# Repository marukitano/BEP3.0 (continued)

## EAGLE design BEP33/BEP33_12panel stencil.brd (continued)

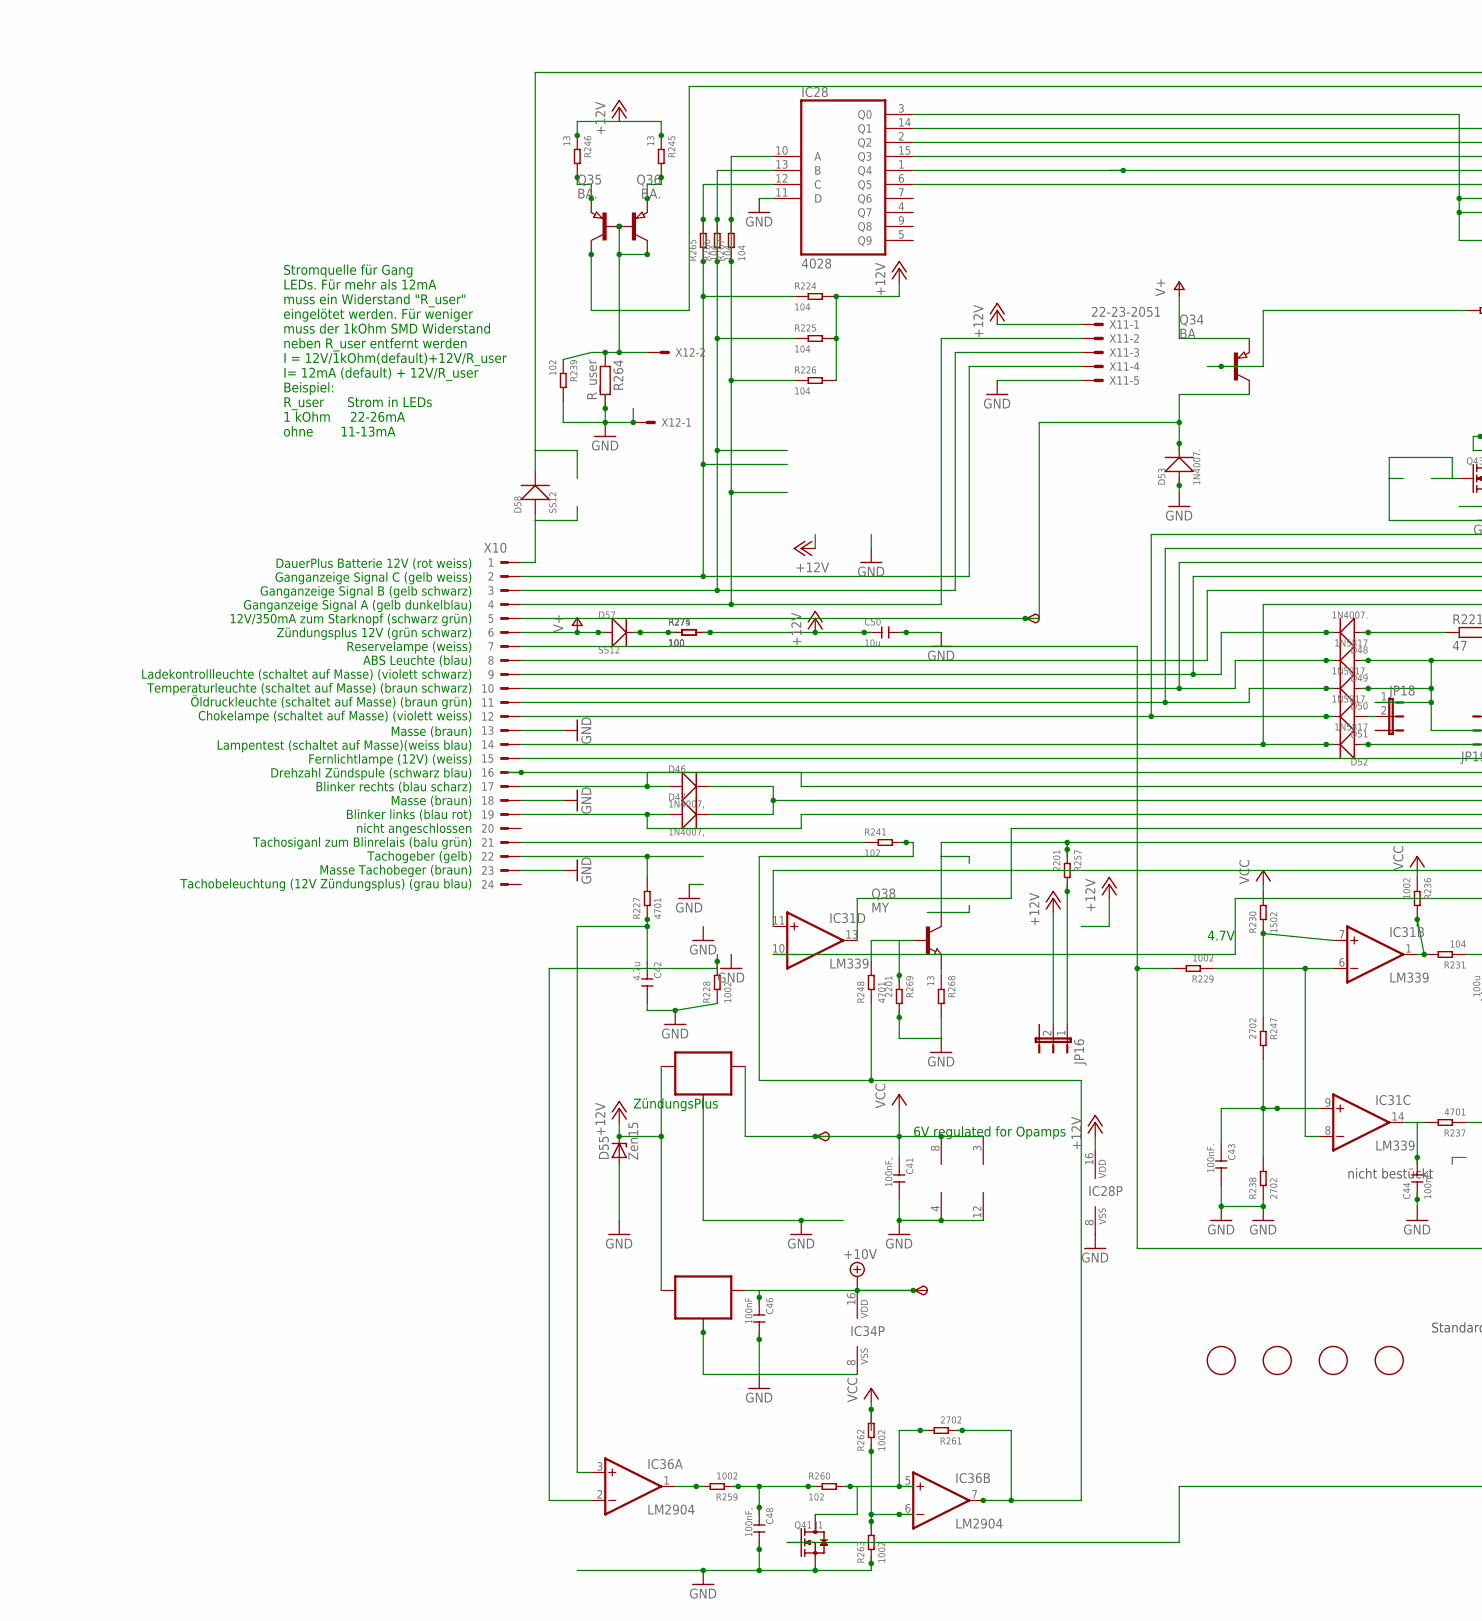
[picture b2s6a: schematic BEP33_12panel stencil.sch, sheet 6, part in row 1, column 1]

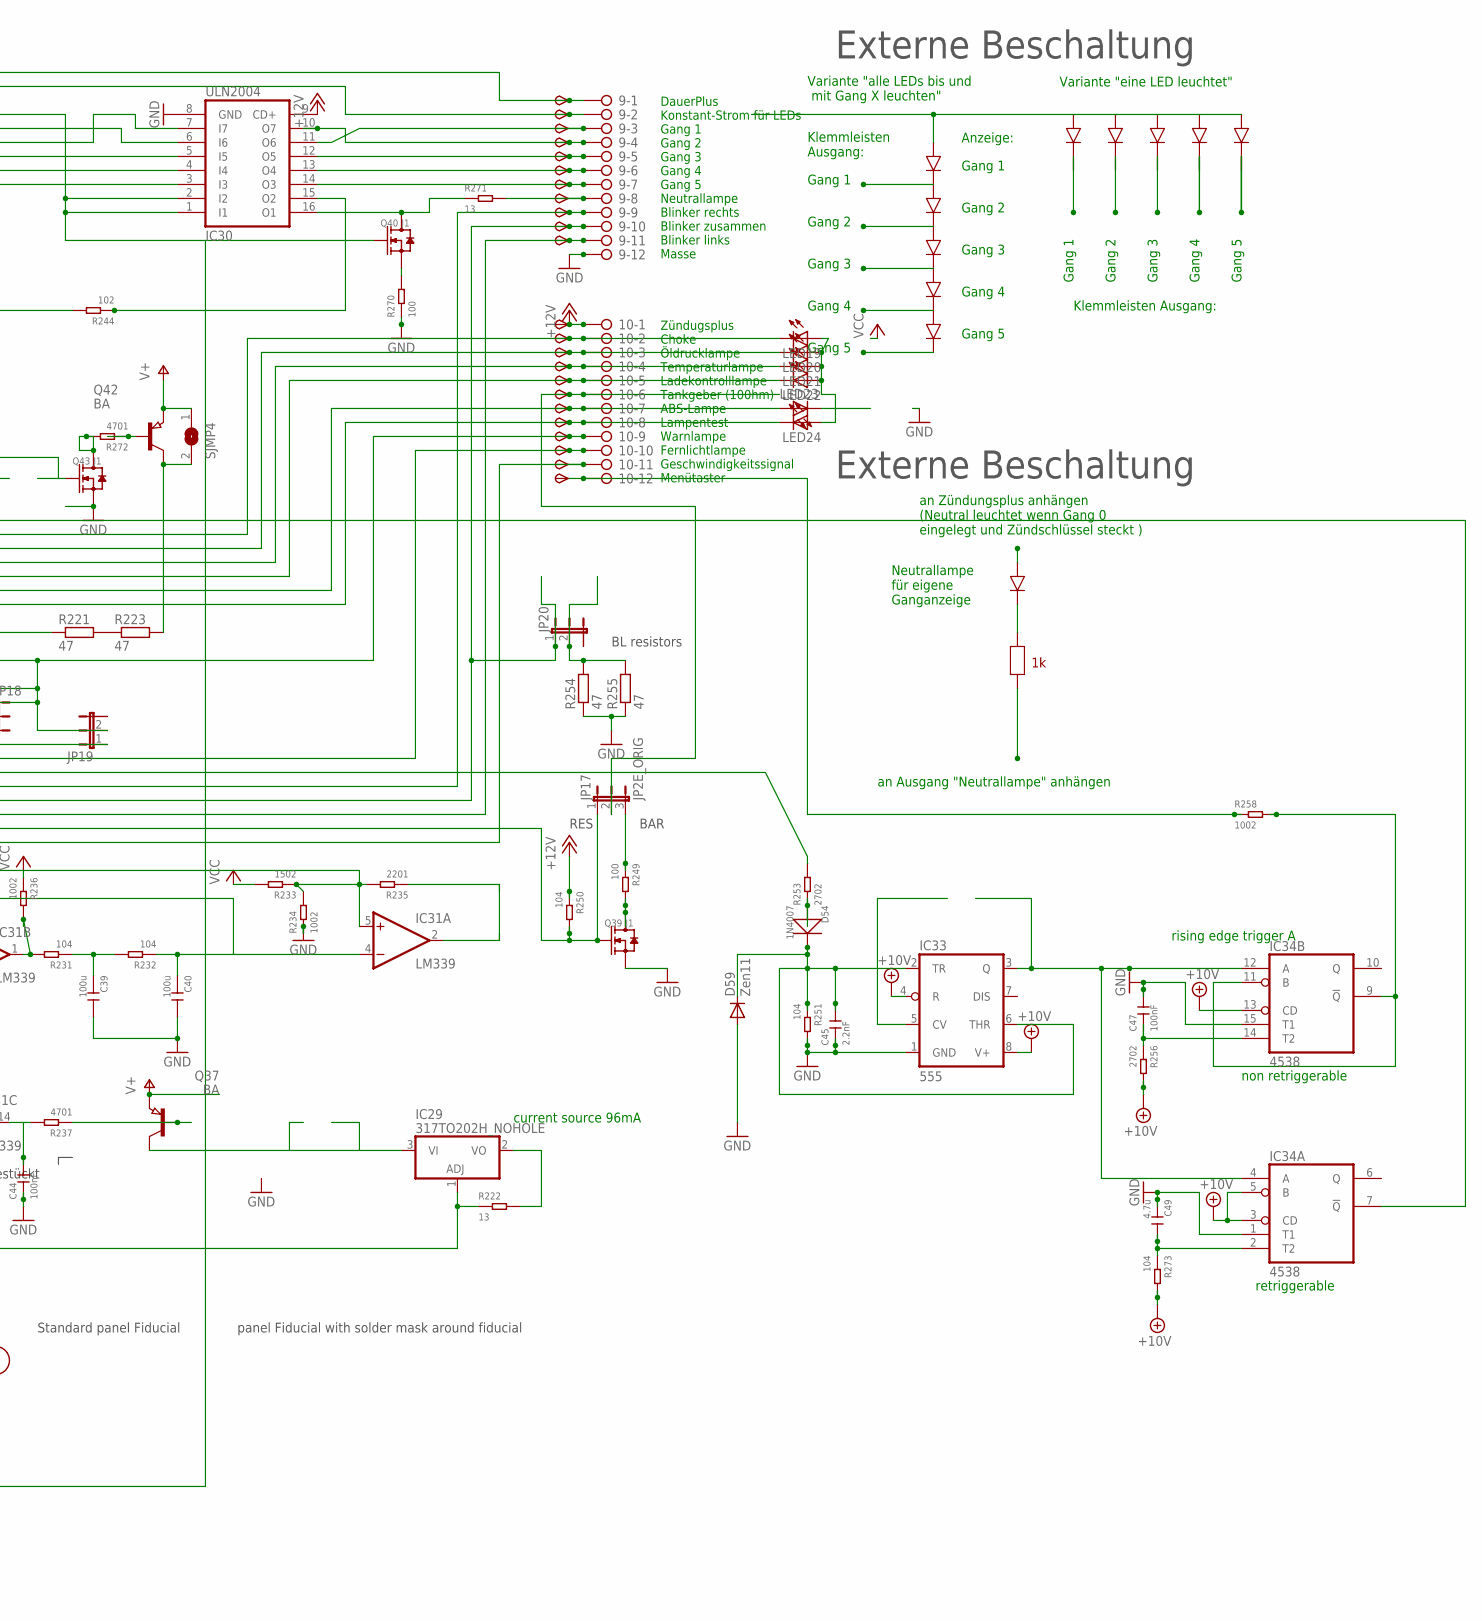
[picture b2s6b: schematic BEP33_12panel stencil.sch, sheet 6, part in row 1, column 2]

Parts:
6V4, 10V4: TPSB2.0; B2.0
9, 10: 2081-1132; 12-PIN
C39, C40: 100u; C1206
C41, C48: 100nF,; C0805
C42, C49: 4.7u; C0805
C43, C44: 100nF.; C0805
C45: 2.2nF; C0805
C46, C47: 100nF; C0805
C50: 10u; C1206
D46, D47: 1N4007,; DO-214AC
D48, D53: 1N4007.; DO-214AC
D49, D52: 1N5817; DO-214AC_SLIM
D50, D51: 1N5817.; DO-214AC_SLIM
D54: 1N4007; DO-214AC
D55: Zen15; DO214AA
D57, D58: SS12; DO-214AC_SLIM
D59: Zen11; SOD-123_MINI-SMA
FID15, FID16, FID17, FID18: FIDUCIAL; FIDUCIAL_1MM
IC28: 4028; SO16
IC29: 317TO202H_NOHOLE; TO220H_NOHOLE
IC30: ULN2004; SO16
IC31: LM339; SO14
IC32: 78L06; SOT89_ROUND
IC33: 555; SO08
IC34: 4538; SO16
IC35: 78L10; SOT89_ROUND
IC36: LM2904; SO08
JP16, JP18, JP19, JP20: JP2EJP2_SMALLPADS; JP2_SMALLPADS
JP17: JP2E_ORIG; JP2_ORIG_SMALLPADS
LED19, LED20, LED21, LED22, LED23, LED24: LEDLD260; LD260
Q34, Q37, Q42: BA; SOT89
Q35, Q36: BA.; SOT89
Q38: MY; SOT89
Q39, Q40, Q41, Q43: J1; SOT-23
R221, R223, R254, R255: 47; V235/17_1MM
R222, R245, R246, R268, R271: 13; R1206
R224, R225, R226, R231, R232, R250, R251, R265, R266, R267, R273: 104; R0805
R227, R237, R248, R272: 4701; R0805
R228, R229, R234, R236, R258, R259, R262, R263: 1002; R0805
R230, R233: 1502; R0805
R235, R257, R269: 2201; R0805
R238, R247, R253, R256, R261: 2702; R0805
R239, R241, R244, R260: 102; R0805
R249, R270, R274, R275: 100; R0805
R264: R_user; R0805
SJMP4: SJ
START4: TPSB2.0; B2.0
TP93, TP94, TP95, TP96, TP97, TP98, TP99, TP100, TP101, TP102, TP103, TP104, TP105, TP106, TP107, TP108, TP109, TP110, TP112, TP113, TP114, TP115: TPSB2.0; B2.0
TP111: TPSB1,27; B1,27
X10: CON_BMWV2; 24-PIN_V2
X11: 22-23-2051
X12: 22-23-2021

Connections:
+10V: 10V4.TP, C46.1, IC33.4 (R), IC33.8 (V+), IC34.3 (CD), IC34.5 (B), IC34.13 (CD), IC34.16 (VDD), IC35.1 (OUT), R256.2, R273.2; also elsewhere on the board
+12V: 10.1, C50.1, D55.C, IC28.16 (VDD), IC30.9 (CD+), IC32.3 (IN), IC35.3 (IN), JP16.2, R224.2, R225.2, R226.2, R245.1, R246.1, R250.1, R274.2, R275.2, TP114.TP, X11.1; also elsewhere on the board
+12V5: 10.11, Q38.2 (C), R257.1, TP113.TP
GND: 9.12, C39.2, C40.2, C41.2, C42.2, C43.2, C44.1, C45.1, C46.2, C47.2, C48.2, C49.1, C50.2, D53.1 (+), D55.A, D59.A, IC28.8 (VSS), IC28.11 (D), IC30.8 (GND), IC31.12 (GND), IC32.2 (GND), IC32.2@1 (GND), IC33.1 (GND), IC34.1 (T1), IC34.8 (VSS), IC34.15 (T1), IC35.2 (GND), IC35.2@1 (GND), IC36.4 (V-), Q39.2 (S), Q41.2 (S), Q43.2 (S), R228.1, R234.1, R238.1, R239.2, R251.2, R254.1, R255.1, R263.1, R264.2, R268.2, R269.2, R270.1, X10.13, X10.18, X10.23, X11.5, X12.1; also elsewhere on the board
unnamed: R221.2, R223.1
unnamed: 10.9, D49.1 (+), D50.1 (+), JP18.1, JP19.2, TP111.TP
unnamed: IC28.10 (A), R226.1, R267.1, R267.2, X10.4, X11.2
unnamed: IC28.13 (B), R225.1, R266.1, R266.2, X10.3, X11.3
unnamed: D53.2 (-), Q34.2 (C), START4.TP, X10.5
unnamed: IC28.12 (C), R224.1, R265.1, R265.2, X10.2, X11.4
unnamed: 10.7, LED23.A, TP109.TP, X10.8
unnamed: 10.2, D51.2 (-), LED19.K (C), TP104.TP, X10.12
unnamed: 10.3, D50.2 (-), LED20.K (C), TP105.TP, X10.11
unnamed: 10.4, D49.2 (-), LED21.K (C), TP106.TP, X10.10
unnamed: 10.8, D52.2 (-), LED24.K (C), TP110.TP, X10.14
unnamed: 9.9, D46.1 (+), TP101.TP, X10.17
unnamed: 9.11, D47.1 (+), TP103.TP, X10.19
unnamed: R227.2, X10.22
unnamed: C42.1, IC36.3 (+IN), R227.1
unnamed: IC31.1 (OUT), R231.2, R236.2
unnamed: C39.1, R231.1, R232.2
unnamed: C40.1, IC31.4 (-IN), IC31.10 (-IN), R232.1
unnamed: IC31.5 (+IN), IC31.11 (+IN), R233.1, R234.2, R235.2
unnamed: C43.1, IC31.9 (+IN), R238.2, R247.2
unnamed: C44.2, IC31.14 (OUT), R237.2
unnamed: Q37.1 (B), R237.1
unnamed: IC28.2 (Q2), IC30.7 (I7)
unnamed: 9.5, IC30.12 (O5), TP97.TP
unnamed: IC28.1 (Q4), IC30.4 (I4)
unnamed: 10.10, TP112.TP, X10.15
unnamed: 10.5, D48.2 (-), LED22.K (C), TP107.TP, X10.9
unnamed: D48.1 (+), R221.1
unnamed: IC28.6 (Q5), IC30.3 (I3)
unnamed: 9.4, IC30.10 (O7), TP96.TP
unnamed: IC29.1 (ADJ), R222.1, R229.2, X10.7
unnamed: IC31.6 (-IN), IC31.8 (-IN), R229.1
unnamed: 9.2, Q36.2 (C), TP94.TP
unnamed: 9.1, D58.2 (-), TP93.TP
unnamed: R253.2, X10.16
unnamed: IC28.15 (Q3), IC30.5 (I5)
unnamed: 9.6, IC30.13 (O4), TP98.TP
unnamed: 9.7, IC30.14 (O3), TP99.TP
unnamed: 10.6, JP17.2, TP108.TP
unnamed: LED19.A, LED20.A, LED21.A, LED22.A, LED24.A
unnamed: Q34.1 (B), R244.2
unnamed: IC28.3 (Q0), IC30.1 (I1), IC30.2 (I2), Q40.1 (G), Q41.1 (G)
unnamed: IC28.14 (Q1), IC30.6 (I6)
unnamed: 9.3, IC30.11 (O6), TP95.TP
unnamed: Q35.1 (B), Q35.2 (C), Q36.1 (B), R239.1, R264.1, X12.2
unnamed: Q36.3 (E), R246.2
unnamed: Q35.3 (E), R245.2
unnamed: IC31.7 (+IN), R230.1, R247.1
unnamed: IC36.2 (-IN), R228.2
unnamed: Q38.1 (B), R248.2, R269.1
unnamed: Q39.3 (D), R249.2
unnamed: IC29.2 (VO), R222.2
unnamed: IC29.3 (VI), Q37.2 (C)
unnamed: IC33.3 (Q), IC34.4 (A), IC34.12 (A)
unnamed: D54.1 (+), R253.1
unnamed: 9.10, D46.2 (-), D47.2 (-), JP20.1, TP102.TP
unnamed: JP20.2, R254.2, R255.2
unnamed: IC34.9 (!Q), IC34.11 (B), R258.2
unnamed: C47.1, IC34.14 (T2), R256.1
unnamed: JP16.1, R257.2
unnamed: IC30.15 (O2), R244.1
unnamed: 10.12, R258.1, TP115.TP
unnamed: D51.1 (+), JP18.2
unnamed: IC36.1 (OUT), R259.2
unnamed: C48.1, R259.1, R260.1
unnamed: IC36.5 (+IN), Q41.3 (D), R260.2, R261.2
unnamed: IC36.6 (-IN), R262.1, R263.2
unnamed: D52.1 (+), JP19.1
unnamed: JP17.3, R249.1
unnamed: IC31.13 (OUT), JP17.1, Q39.1 (G), R250.2
unnamed: R241.1, X10.21
unnamed: IC30.16 (O1), Q40.3 (D), R271.1
unnamed: D57.2 (-), R274.1, R275.1
unnamed: 9.8, R271.2, TP100.TP
unnamed: Q40.2 (S), R270.2
unnamed: D58.1 (+), X10.1
unnamed: Q38.3 (E), R268.1
unnamed: C45.2, D54.2 (-), D59.C, IC33.2 (TR), IC33.6 (THR), R251.1
unnamed: Q42.1 (B), R272.1
unnamed: Q43.3 (D), R272.2
unnamed: Q42.2 (C), R223.2, SJMP4.2
unnamed: IC36.7 (OUT), R241.2, R248.1, R261.1
unnamed: IC31.2 (OUT), R235.1
unnamed: IC34.7 (!Q), Q43.1 (G)
unnamed: C49.2, IC34.2 (T2), R273.1
V+: D57.1 (+), Q34.3 (E), Q37.3 (E), Q42.3 (E), SJMP4.1, X10.6; also elsewhere on the board
VCC: 6V4.TP, C41.1, IC31.3 (V+), IC32.1 (OUT), IC36.8 (V+), R230.2, R233.2, R236.1, R262.2; also elsewhere on the board

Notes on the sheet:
6V regulated for Opamps
current source 96mA
ZündungsPlus
Zündugsplus Choke Öldrucklampe Temperaturlampe Ladekontrolllampe Tankgeber (100hm) ABS-Lampe Lampentest Warnlampe Fernlichtlampe Geschwindigkeitssignal Menütaster
DauerPlus Konstant-Strom für LEDs Gang 1 Gang 2 Gang 3 Gang 4 Gang 5 Neutrallampe Blinker rechts Blinker zusammen Blinker links Masse
DauerPlus Batterie 12V (rot weiss) Ganganzeige Signal C (gelb weiss) Ganganzeige Signal B (gelb schwarz) Ganganzeige Signal A (gelb dunkelblau) 12V/350mA zum Starknopf (schwarz grün) Zündungsplus 12V (grün schwarz) Reservelampe (weiss) ABS Leuchte (blau) Ladekontrollleuchte (schaltet auf Masse) (vi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
Masse (braun) Lampentest (schaltet auf Masse)(weiss blau) Fernlichtlampe (12V) (weiss) Drehzahl Zündspule (schwarz blau) Blinker rechts (blau scharz) Masse (braun) Blinker links (blau rot) nicht angeschlossen Tachosiganl zum Blinrelais (balu grün) Tachogeber (gelb) Masse Tachobeger (braun) Tachobel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
4.7V
Stromquelle für Gang LEDs. Für mehr als 12mA muss ein Widerstand "R_user" eingelötet werden. Für weniger muss der 1kOhm SMD Widerstand neben R_user entfernt werden I = 12V/1kOhm(default)+12V/R_user I= 12mA (default) + 12V/R_user Beispiel: R_user Strom in LEDs 1 kOhm 22-26mA ohne 11-13mA
Gang 1
Gang 2
Gang 3
Gang 4
Gang 5
Variante "eine LED leuchtet"
Variante "alle LEDs bis und mit Gang X leuchten"
Klemmleisten Ausgang:
Klemmleisten Ausgang:
an Zündungsplus anhängen (Neutral leuchtet wenn Gang 0 eingelegt und Zündschlüssel steckt )
an Ausgang "Neutrallampe" anhängen
Neutrallampe für eigene Ganganzeige
Externe Beschaltung
Anzeige:
nicht bestückt
rising edge trigger A
BAR
RES
BL resistors
Standard panel Fiducial
panel Fiducial with solder mask around fiducial
non retriggerable
retriggerable

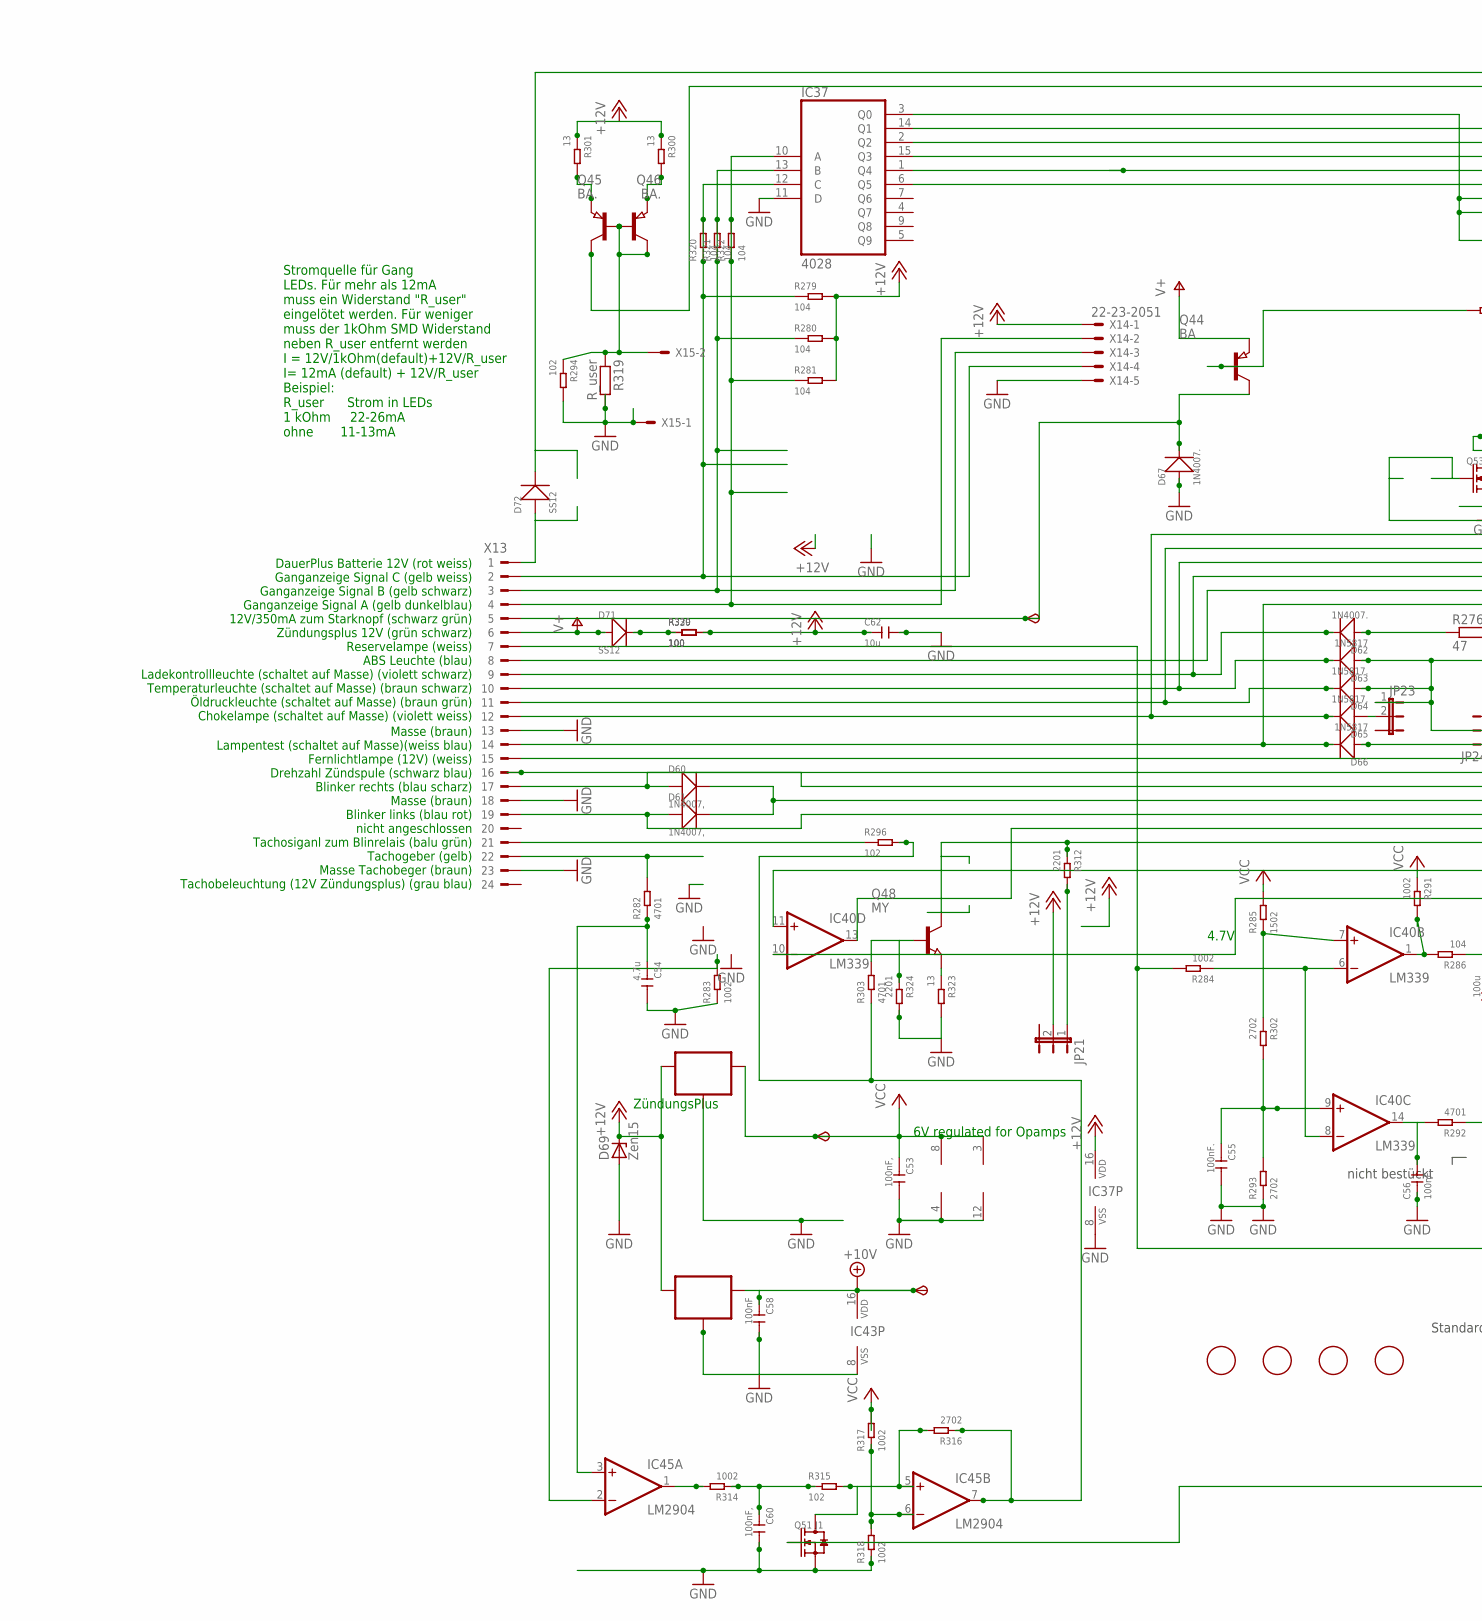
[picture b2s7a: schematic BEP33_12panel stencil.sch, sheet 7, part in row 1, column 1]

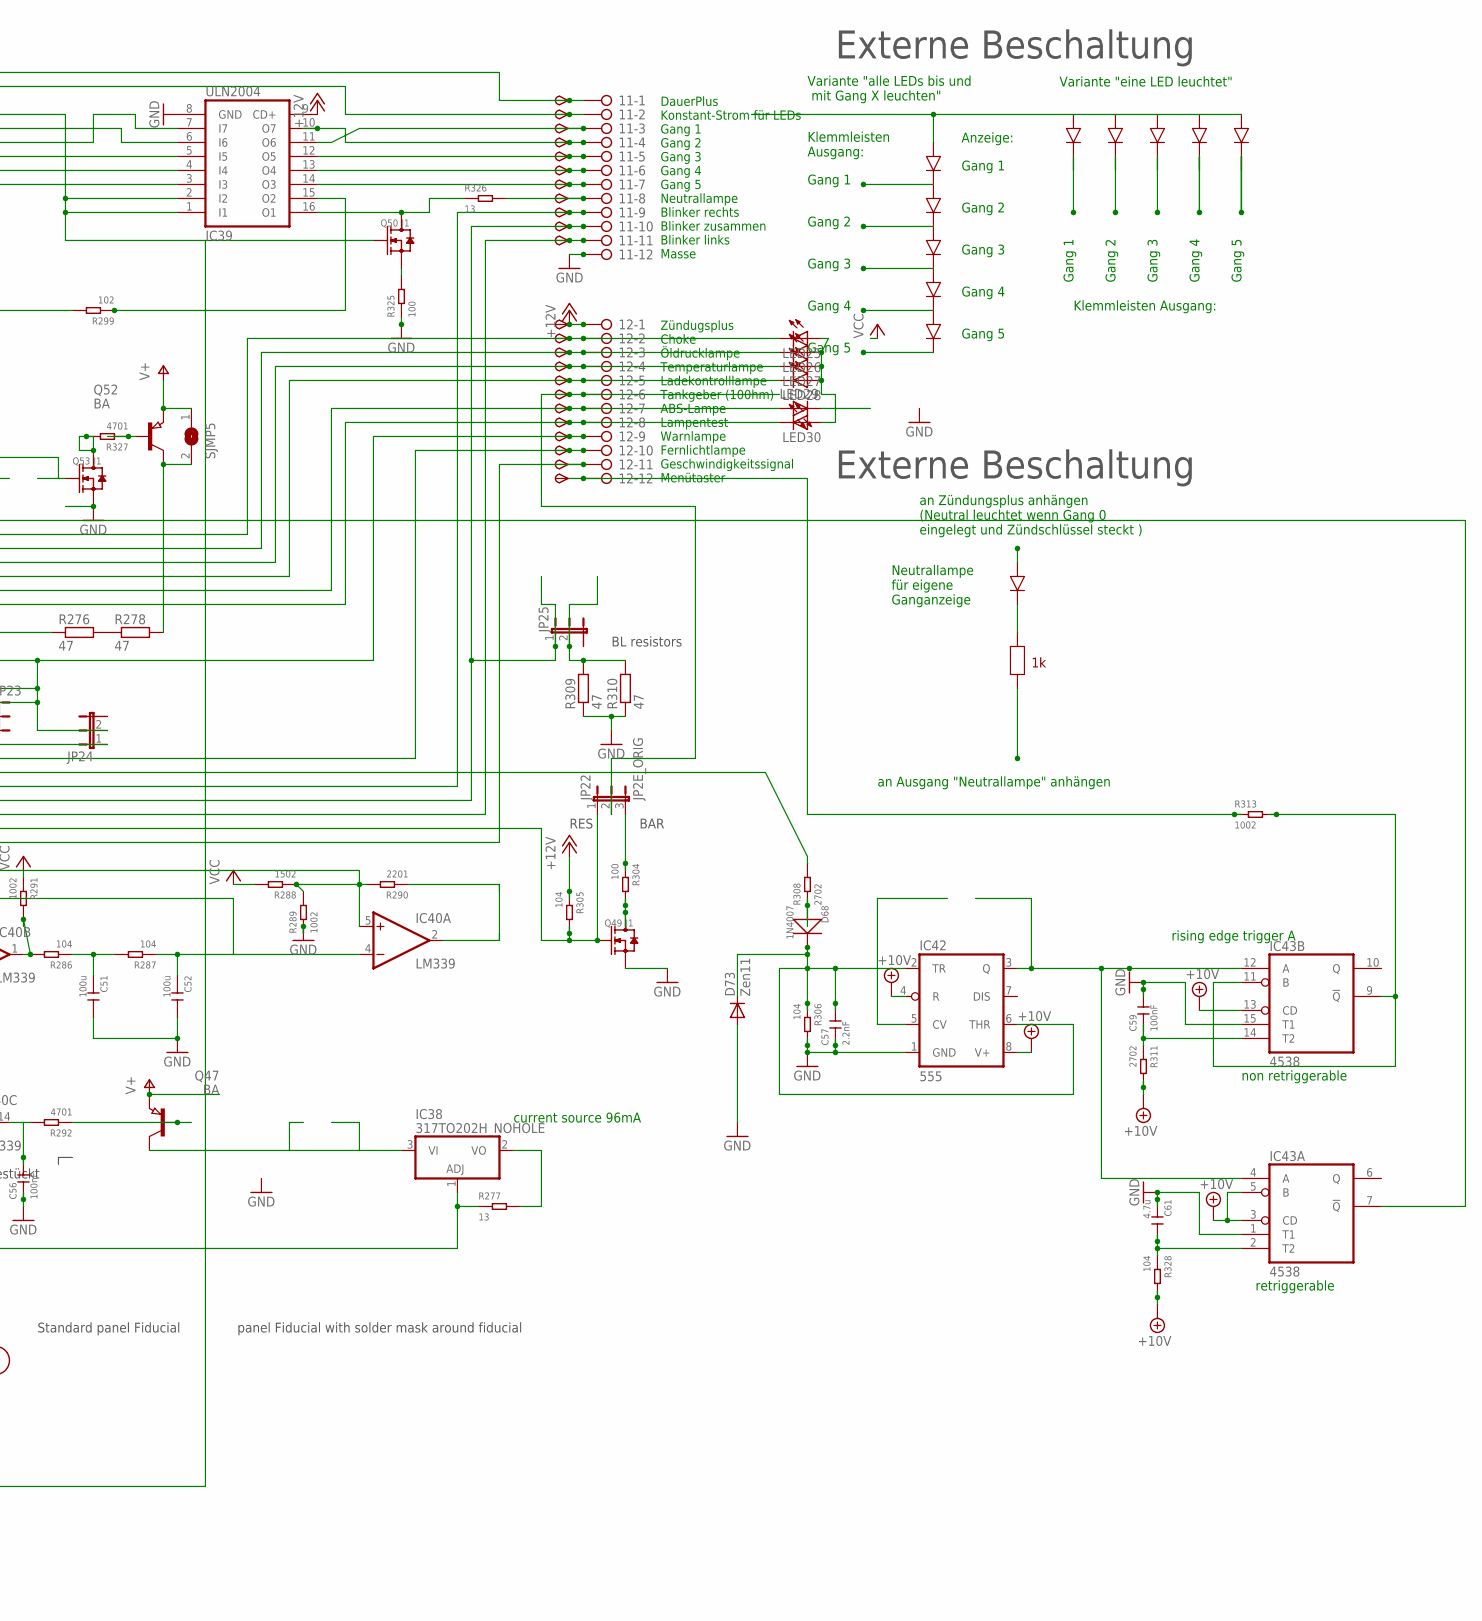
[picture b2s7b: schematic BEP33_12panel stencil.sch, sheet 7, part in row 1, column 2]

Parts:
6V5, 10V5: TPSB2.0; B2.0
11, 12: 2081-1132; 12-PIN
C51, C52: 100u; C1206
C53, C60: 100nF,; C0805
C54, C61: 4.7u; C0805
C55, C56: 100nF.; C0805
C57: 2.2nF; C0805
C58, C59: 100nF; C0805
C62: 10u; C1206
D60, D61: 1N4007,; DO-214AC
D62, D67: 1N4007.; DO-214AC
D63, D66: 1N5817; DO-214AC_SLIM
D64, D65: 1N5817.; DO-214AC_SLIM
D68: 1N4007; DO-214AC
D69: Zen15; DO214AA
D71, D72: SS12; DO-214AC_SLIM
D73: Zen11; SOD-123_MINI-SMA
FID19, FID20, FID21, FID22: FIDUCIAL; FIDUCIAL_1MM
IC37: 4028; SO16
IC38: 317TO202H_NOHOLE; TO220H_NOHOLE
IC39: ULN2004; SO16
IC40: LM339; SO14
IC41: 78L06; SOT89_ROUND
IC42: 555; SO08
IC43: 4538; SO16
IC44: 78L10; SOT89_ROUND
IC45: LM2904; SO08
JP21, JP23, JP24, JP25: JP2EJP2_SMALLPADS; JP2_SMALLPADS
JP22: JP2E_ORIG; JP2_ORIG_SMALLPADS
LED25, LED26, LED27, LED28, LED29, LED30: LEDLD260; LD260
Q44, Q47, Q52: BA; SOT89
Q45, Q46: BA.; SOT89
Q48: MY; SOT89
Q49, Q50, Q51, Q53: J1; SOT-23
R276, R278, R309, R310: 47; V235/17_1MM
R277, R300, R301, R323, R326: 13; R1206
R279, R280, R281, R286, R287, R305, R306, R320, R321, R322, R328: 104; R0805
R282, R292, R303, R327: 4701; R0805
R283, R284, R289, R291, R313, R314, R317, R318: 1002; R0805
R285, R288: 1502; R0805
R290, R312, R324: 2201; R0805
R293, R302, R308, R311, R316: 2702; R0805
R294, R296, R299, R315: 102; R0805
R304, R325, R329, R330: 100; R0805
R319: R_user; R0805
SJMP5: SJ
START5: TPSB2.0; B2.0
TP116, TP117, TP118, TP119, TP120, TP121, TP122, TP123, TP124, TP125, TP126, TP127, TP128, TP129, TP130, TP131, TP132, TP133, TP135, TP136, TP137, TP138: TPSB2.0; B2.0
TP134: TPSB1,27; B1,27
X13: CON_BMWV2; 24-PIN_V2
X14: 22-23-2051
X15: 22-23-2021

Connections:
+10V: 10V5.TP, C58.1, IC42.4 (R), IC42.8 (V+), IC43.3 (CD), IC43.5 (B), IC43.13 (CD), IC43.16 (VDD), IC44.1 (OUT), R311.2, R328.2; also elsewhere on the board
+12V: 12.1, C62.1, D69.C, IC37.16 (VDD), IC39.9 (CD+), IC41.3 (IN), IC44.3 (IN), JP21.2, R279.2, R280.2, R281.2, R300.1, R301.1, R305.1, R329.2, R330.2, TP137.TP, X14.1; also elsewhere on the board
+12V6: 12.11, Q48.2 (C), R312.1, TP136.TP
GND: 11.12, C51.2, C52.2, C53.2, C54.2, C55.2, C56.1, C57.1, C58.2, C59.2, C60.2, C61.1, C62.2, D67.1 (+), D69.A, D73.A, IC37.8 (VSS), IC37.11 (D), IC39.8 (GND), IC40.12 (GND), IC41.2 (GND), IC41.2@1 (GND), IC42.1 (GND), IC43.1 (T1), IC43.8 (VSS), IC43.15 (T1), IC44.2 (GND), IC44.2@1 (GND), IC45.4 (V-), Q49.2 (S), Q51.2 (S), Q53.2 (S), R283.1, R289.1, R293.1, R294.2, R306.2, R309.1, R310.1, R318.1, R319.2, R323.2, R324.2, R325.1, X13.13, X13.18, X13.23, X14.5, X15.1; also elsewhere on the board
unnamed: R276.2, R278.1
unnamed: 12.9, D63.1 (+), D64.1 (+), JP23.1, JP24.2, TP134.TP
unnamed: IC37.10 (A), R281.1, R322.1, R322.2, X13.4, X14.2
unnamed: IC37.13 (B), R280.1, R321.1, R321.2, X13.3, X14.3
unnamed: D67.2 (-), Q44.2 (C), START5.TP, X13.5
unnamed: IC37.12 (C), R279.1, R320.1, R320.2, X13.2, X14.4
unnamed: 12.7, LED29.A, TP132.TP, X13.8
unnamed: 12.2, D65.2 (-), LED25.K (C), TP127.TP, X13.12
unnamed: 12.3, D64.2 (-), LED26.K (C), TP128.TP, X13.11
unnamed: 12.4, D63.2 (-), LED27.K (C), TP129.TP, X13.10
unnamed: 12.8, D66.2 (-), LED30.K (C), TP133.TP, X13.14
unnamed: 11.9, D60.1 (+), TP124.TP, X13.17
unnamed: 11.11, D61.1 (+), TP126.TP, X13.19
unnamed: R282.2, X13.22
unnamed: C54.1, IC45.3 (+IN), R282.1
unnamed: IC40.1 (OUT), R286.2, R291.2
unnamed: C51.1, R286.1, R287.2
unnamed: C52.1, IC40.4 (-IN), IC40.10 (-IN), R287.1
unnamed: IC40.5 (+IN), IC40.11 (+IN), R288.1, R289.2, R290.2
unnamed: C55.1, IC40.9 (+IN), R293.2, R302.2
unnamed: C56.2, IC40.14 (OUT), R292.2
unnamed: Q47.1 (B), R292.1
unnamed: IC37.2 (Q2), IC39.7 (I7)
unnamed: 11.5, IC39.12 (O5), TP120.TP
unnamed: IC37.1 (Q4), IC39.4 (I4)
unnamed: 12.10, TP135.TP, X13.15
unnamed: 12.5, D62.2 (-), LED28.K (C), TP130.TP, X13.9
unnamed: D62.1 (+), R276.1
unnamed: IC37.6 (Q5), IC39.3 (I3)
unnamed: 11.4, IC39.10 (O7), TP119.TP
unnamed: IC38.1 (ADJ), R277.1, R284.2, X13.7
unnamed: IC40.6 (-IN), IC40.8 (-IN), R284.1
unnamed: 11.2, Q46.2 (C), TP117.TP
unnamed: 11.1, D72.2 (-), TP116.TP
unnamed: R308.2, X13.16
unnamed: IC37.15 (Q3), IC39.5 (I5)
unnamed: 11.6, IC39.13 (O4), TP121.TP
unnamed: 11.7, IC39.14 (O3), TP122.TP
unnamed: 12.6, JP22.2, TP131.TP
unnamed: LED25.A, LED26.A, LED27.A, LED28.A, LED30.A
unnamed: Q44.1 (B), R299.2
unnamed: IC37.3 (Q0), IC39.1 (I1), IC39.2 (I2), Q50.1 (G), Q51.1 (G)
unnamed: IC37.14 (Q1), IC39.6 (I6)
unnamed: 11.3, IC39.11 (O6), TP118.TP
unnamed: Q45.1 (B), Q45.2 (C), Q46.1 (B), R294.1, R319.1, X15.2
unnamed: Q46.3 (E), R301.2
unnamed: Q45.3 (E), R300.2
unnamed: IC40.7 (+IN), R285.1, R302.1
unnamed: IC45.2 (-IN), R283.2
unnamed: Q48.1 (B), R303.2, R324.1
unnamed: Q49.3 (D), R304.2
unnamed: IC38.2 (VO), R277.2
unnamed: IC38.3 (VI), Q47.2 (C)
unnamed: IC42.3 (Q), IC43.4 (A), IC43.12 (A)
unnamed: D68.1 (+), R308.1
unnamed: 11.10, D60.2 (-), D61.2 (-), JP25.1, TP125.TP
unnamed: JP25.2, R309.2, R310.2
unnamed: IC43.9 (!Q), IC43.11 (B), R313.2
unnamed: C59.1, IC43.14 (T2), R311.1
unnamed: JP21.1, R312.2
unnamed: IC39.15 (O2), R299.1
unnamed: 12.12, R313.1, TP138.TP
unnamed: D65.1 (+), JP23.2
unnamed: IC45.1 (OUT), R314.2
unnamed: C60.1, R314.1, R315.1
unnamed: IC45.5 (+IN), Q51.3 (D), R315.2, R316.2
unnamed: IC45.6 (-IN), R317.1, R318.2
unnamed: D66.1 (+), JP24.1
unnamed: JP22.3, R304.1
unnamed: IC40.13 (OUT), JP22.1, Q49.1 (G), R305.2
unnamed: R296.1, X13.21
unnamed: IC39.16 (O1), Q50.3 (D), R326.1
unnamed: D71.2 (-), R329.1, R330.1
unnamed: 11.8, R326.2, TP123.TP
unnamed: Q50.2 (S), R325.2
unnamed: D72.1 (+), X13.1
unnamed: Q48.3 (E), R323.1
unnamed: C57.2, D68.2 (-), D73.C, IC42.2 (TR), IC42.6 (THR), R306.1
unnamed: Q52.1 (B), R327.1
unnamed: Q53.3 (D), R327.2
unnamed: Q52.2 (C), R278.2, SJMP5.2
unnamed: IC45.7 (OUT), R296.2, R303.1, R316.1
unnamed: IC40.2 (OUT), R290.1
unnamed: IC43.7 (!Q), Q53.1 (G)
unnamed: C61.2, IC43.2 (T2), R328.1
V+: D71.1 (+), Q44.3 (E), Q47.3 (E), Q52.3 (E), SJMP5.1, X13.6; also elsewhere on the board
VCC: 6V5.TP, C53.1, IC40.3 (V+), IC41.1 (OUT), IC45.8 (V+), R285.2, R288.2, R291.1, R317.2; also elsewhere on the board

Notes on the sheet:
6V regulated for Opamps
current source 96mA
ZündungsPlus
Zündugsplus Choke Öldrucklampe Temperaturlampe Ladekontrolllampe Tankgeber (100hm) ABS-Lampe Lampentest Warnlampe Fernlichtlampe Geschwindigkeitssignal Menütaster
DauerPlus Konstant-Strom für LEDs Gang 1 Gang 2 Gang 3 Gang 4 Gang 5 Neutrallampe Blinker rechts Blinker zusammen Blinker links Masse
DauerPlus Batterie 12V (rot weiss) Ganganzeige Signal C (gelb weiss) Ganganzeige Signal B (gelb schwarz) Ganganzeige Signal A (gelb dunkelblau) 12V/350mA zum Starknopf (schwarz grün) Zündungsplus 12V (grün schwarz) Reservelampe (weiss) ABS Leuchte (blau) Ladekontrollleuchte (schaltet auf Masse) (vi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
Masse (braun) Lampentest (schaltet auf Masse)(weiss blau) Fernlichtlampe (12V) (weiss) Drehzahl Zündspule (schwarz blau) Blinker rechts (blau scharz) Masse (braun) Blinker links (blau rot) nicht angeschlossen Tachosiganl zum Blinrelais (balu grün) Tachogeber (gelb) Masse Tachobeger (braun) Tachobel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
4.7V
Stromquelle für Gang LEDs. Für mehr als 12mA muss ein Widerstand "R_user" eingelötet werden. Für weniger muss der 1kOhm SMD Widerstand neben R_user entfernt werden I = 12V/1kOhm(default)+12V/R_user I= 12mA (default) + 12V/R_user Beispiel: R_user Strom in LEDs 1 kOhm 22-26mA ohne 11-13mA
Gang 1
Gang 2
Gang 3
Gang 4
Gang 5
Variante "eine LED leuchtet"
Variante "alle LEDs bis und mit Gang X leuchten"
Klemmleisten Ausgang:
Klemmleisten Ausgang:
an Zündungsplus anhängen (Neutral leuchtet wenn Gang 0 eingelegt und Zündschlüssel steckt )
an Ausgang "Neutrallampe" anhängen
Neutrallampe für eigene Ganganzeige
Externe Beschaltung
Anzeige:
nicht bestückt
rising edge trigger A
BAR
RES
BL resistors
Standard panel Fiducial
panel Fiducial with solder mask around fiducial
non retriggerable
retriggerable

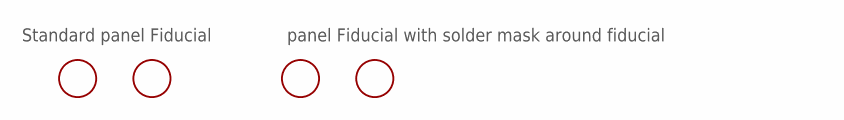
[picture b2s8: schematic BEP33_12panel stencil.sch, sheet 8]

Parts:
FID1B1, FID2B1: FIDUCIALFIDUCIAL_1MM_WITH_SOLDERMASK; FIDUCIAL_1MM_WITH_SOLDERMASK
FID23, FID24: FIDUCIAL; FIDUCIAL_1MM

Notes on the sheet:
Standard panel Fiducial
panel Fiducial with solder mask around fiducial

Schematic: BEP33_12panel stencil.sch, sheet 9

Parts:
6V6, 10V6: TPSB2.0; B2.0
13, 14: 2081-1132; 12-PIN
C63, C64: 100u; C1206
C65, C72: 100nF,; C0805
C66, C73: 4.7u; C0805
C67, C68: 100nF.; C0805
C69: 2.2nF; C0805
C70, C71: 100nF; C0805
C74: 10u; C1206
D14, D28: 1N4007,; DO-214AC
D42, D76: 1N4007.; DO-214AC
D56, D75: 1N5817; DO-214AC_SLIM
D70, D74: 1N5817.; DO-214AC_SLIM
D77: 1N4007; DO-214AC
D78: Zen15; DO214AA
D79, D80: SS12; DO-214AC_SLIM
D81: Zen11; SOD-123_MINI-SMA
FID25, FID26, FID27, FID28: FIDUCIAL; FIDUCIAL_1MM
IC46: 4028; SO16
IC47: 317TO202H_NOHOLE; TO220H_NOHOLE
IC48: ULN2004; SO16
IC49: LM339; SO14
IC50: 78L06; SOT89_ROUND
IC51: 555; SO08
IC52: 4538; SO16
IC53: 78L10; SOT89_ROUND
IC54: LM2904; SO08
JP26, JP28, JP29, JP30: JP2EJP2_SMALLPADS; JP2_SMALLPADS
JP27: JP2E_ORIG; JP2_ORIG_SMALLPADS
LED31, LED32, LED33, LED34, LED35, LED36: LEDLD260; LD260
Q54, Q57, Q62: BA; SOT89
Q55, Q56: BA.; SOT89
Q58: MY; SOT89
Q59, Q60, Q61, Q63: J1; SOT-23
R31, R34, R336, R337: 47; V235/17_1MM
R33, R297, R298, R350, R353: 13; R1206
R43, R86, R88, R143, R144, R333, R334, R347, R348, R349, R355: 104; R0805
R89, R240, R331, R354: 4701; R0805
R98, R104, R187, R197, R340, R341, R344, R345: 1002; R0805
R142, R185: 1502; R0805
R188, R339, R351: 2201; R0805
R242, R307, R335, R338, R343: 2702; R0805
R243, R252, R295, R342: 102; R0805
R332, R352, R356, R357: 100; R0805
R346: R_user; R0805
SJMP6: SJ
START6: TPSB2.0; B2.0
TP139, TP140, TP141, TP142, TP143, TP144, TP145, TP146, TP147, TP148, TP149, TP150, TP151, TP152, TP153, TP154, TP155, TP156, TP158, TP159, TP160, TP161: TPSB2.0; B2.0
TP157: TPSB1,27; B1,27
U$25, U$30, U$33, U$34: STC; STENCIL_HOLE
X16: CON_BMWV2; 24-PIN_V2
X17: 22-23-2051
X18: 22-23-2021

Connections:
+10V: 10V6.TP, C70.1, IC51.4 (R), IC51.8 (V+), IC52.3 (CD), IC52.5 (B), IC52.13 (CD), IC52.16 (VDD), IC53.1 (OUT), R338.2, R355.2; also elsewhere on the board
+12V: 14.1, C74.1, D78.C, IC46.16 (VDD), IC48.9 (CD+), IC50.3 (IN), IC53.3 (IN), JP26.2, R43.2, R86.2, R88.2, R297.1, R298.1, R333.1, R356.2, R357.2, TP160.TP, X17.1; also elsewhere on the board
+12V7: 14.11, Q58.2 (C), R339.1, TP159.TP
GND: 13.12, C63.2, C64.2, C65.2, C66.2, C67.2, C68.1, C69.1, C70.2, C71.2, C72.2, C73.1, C74.2, D76.1 (+), D78.A, D81.A, IC46.8 (VSS), IC46.11 (D), IC48.8 (GND), IC49.12 (GND), IC50.2 (GND), IC50.2@1 (GND), IC51.1 (GND), IC52.1 (T1), IC52.8 (VSS), IC52.15 (T1), IC53.2 (GND), IC53.2@1 (GND), IC54.4 (V-), Q59.2 (S), Q61.2 (S), Q63.2 (S), R98.1, R187.1, R242.1, R243.2, R334.2, R336.1, R337.1, R345.1, R346.2, R350.2, R351.2, R352.1, X16.13, X16.18, X16.23, X17.5, X18.1; also elsewhere on the board
unnamed: R31.2, R34.1
unnamed: 14.9, D56.1 (+), D70.1 (+), JP28.1, JP29.2, TP157.TP
unnamed: IC46.10 (A), R88.1, R349.1, R349.2, X16.4, X17.2
unnamed: IC46.13 (B), R86.1, R348.1, R348.2, X16.3, X17.3
unnamed: D76.2 (-), Q54.2 (C), START6.TP, X16.5
unnamed: IC46.12 (C), R43.1, R347.1, R347.2, X16.2, X17.4
unnamed: 14.7, LED35.A, TP155.TP, X16.8
unnamed: 14.2, D74.2 (-), LED31.K (C), TP150.TP, X16.12
unnamed: 14.3, D70.2 (-), LED32.K (C), TP151.TP, X16.11
unnamed: 14.4, D56.2 (-), LED33.K (C), TP152.TP, X16.10
unnamed: 14.8, D75.2 (-), LED36.K (C), TP156.TP, X16.14
unnamed: 13.9, D14.1 (+), TP147.TP, X16.17
unnamed: 13.11, D28.1 (+), TP149.TP, X16.19
unnamed: R89.2, X16.22
unnamed: C66.1, IC54.3 (+IN), R89.1
unnamed: IC49.1 (OUT), R143.2, R197.2
unnamed: C63.1, R143.1, R144.2
unnamed: C64.1, IC49.4 (-IN), IC49.10 (-IN), R144.1
unnamed: IC49.5 (+IN), IC49.11 (+IN), R185.1, R187.2, R188.2
unnamed: C67.1, IC49.9 (+IN), R242.2, R307.2
unnamed: C68.2, IC49.14 (OUT), R240.2
unnamed: Q57.1 (B), R240.1
unnamed: IC46.2 (Q2), IC48.7 (I7)
unnamed: 13.5, IC48.12 (O5), TP143.TP
unnamed: IC46.1 (Q4), IC48.4 (I4)
unnamed: 14.10, TP158.TP, X16.15
unnamed: 14.5, D42.2 (-), LED34.K (C), TP153.TP, X16.9
unnamed: D42.1 (+), R31.1
unnamed: IC46.6 (Q5), IC48.3 (I3)
unnamed: 13.4, IC48.10 (O7), TP142.TP
unnamed: IC47.1 (ADJ), R33.1, R104.2, X16.7
unnamed: IC49.6 (-IN), IC49.8 (-IN), R104.1
unnamed: 13.2, Q56.2 (C), TP140.TP
unnamed: 13.1, D80.2 (-), TP139.TP
unnamed: R335.2, X16.16
unnamed: IC46.15 (Q3), IC48.5 (I5)
unnamed: 13.6, IC48.13 (O4), TP144.TP
unnamed: 13.7, IC48.14 (O3), TP145.TP
unnamed: 14.6, JP27.2, TP154.TP
unnamed: LED31.A, LED32.A, LED33.A, LED34.A, LED36.A
unnamed: Q54.1 (B), R295.2
unnamed: IC46.3 (Q0), IC48.1 (I1), IC48.2 (I2), Q60.1 (G), Q61.1 (G)
unnamed: IC46.14 (Q1), IC48.6 (I6)
unnamed: 13.3, IC48.11 (O6), TP141.TP
unnamed: Q55.1 (B), Q55.2 (C), Q56.1 (B), R243.1, R346.1, X18.2
unnamed: Q56.3 (E), R298.2
unnamed: Q55.3 (E), R297.2
unnamed: IC49.7 (+IN), R142.1, R307.1
unnamed: IC54.2 (-IN), R98.2
unnamed: Q58.1 (B), R331.2, R351.1
unnamed: Q59.3 (D), R332.2
unnamed: IC47.2 (VO), R33.2
unnamed: IC47.3 (VI), Q57.2 (C)
unnamed: IC51.3 (Q), IC52.4 (A), IC52.12 (A)
unnamed: D77.1 (+), R335.1
unnamed: 13.10, D14.2 (-), D28.2 (-), JP30.1, TP148.TP
unnamed: JP30.2, R336.2, R337.2
unnamed: IC52.9 (!Q), IC52.11 (B), R340.2
unnamed: C71.1, IC52.14 (T2), R338.1
unnamed: JP26.1, R339.2
unnamed: IC48.15 (O2), R295.1
unnamed: 14.12, R340.1, TP161.TP
unnamed: D74.1 (+), JP28.2
unnamed: IC54.1 (OUT), R341.2
unnamed: C72.1, R341.1, R342.1
unnamed: IC54.5 (+IN), Q61.3 (D), R342.2, R343.2
unnamed: IC54.6 (-IN), R344.1, R345.2
unnamed: D75.1 (+), JP29.1
unnamed: JP27.3, R332.1
unnamed: IC49.13 (OUT), JP27.1, Q59.1 (G), R333.2
unnamed: R252.1, X16.21
unnamed: IC48.16 (O1), Q60.3 (D), R353.1
unnamed: D79.2 (-), R356.1, R357.1
unnamed: 13.8, R353.2, TP146.TP
unnamed: Q60.2 (S), R352.2
unnamed: D80.1 (+), X16.1
unnamed: Q58.3 (E), R350.1
unnamed: C69.2, D77.2 (-), D81.C, IC51.2 (TR), IC51.6 (THR), R334.1
unnamed: Q62.1 (B), R354.1
unnamed: Q63.3 (D), R354.2
unnamed: Q62.2 (C), R34.2, SJMP6.2
unnamed: IC54.7 (OUT), R252.2, R331.1, R343.1
unnamed: IC49.2 (OUT), R188.1
unnamed: IC52.7 (!Q), Q63.1 (G)
unnamed: C73.2, IC52.2 (T2), R355.1
V+: D79.1 (+), Q54.3 (E), Q57.3 (E), Q62.3 (E), SJMP6.1, X16.6; also elsewhere on the board
VCC: 6V6.TP, C65.1, IC49.3 (V+), IC50.1 (OUT), IC54.8 (V+), R142.2, R185.2, R197.1, R344.2; also elsewhere on the board

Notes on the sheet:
6V regulated for Opamps
current source 96mA
ZündungsPlus
Zündugsplus Choke Öldrucklampe Temperaturlampe Ladekontrolllampe Tankgeber (100hm) ABS-Lampe Lampentest Warnlampe Fernlichtlampe Geschwindigkeitssignal Menütaster
DauerPlus Konstant-Strom für LEDs Gang 1 Gang 2 Gang 3 Gang 4 Gang 5 Neutrallampe Blinker rechts Blinker zusammen Blinker links Masse
DauerPlus Batterie 12V (rot weiss) Ganganzeige Signal C (gelb weiss) Ganganzeige Signal B (gelb schwarz) Ganganzeige Signal A (gelb dunkelblau) 12V/350mA zum Starknopf (schwarz grün) Zündungsplus 12V (grün schwarz) Reservelampe (weiss) ABS Leuchte (blau) Ladekontrollleuchte (schaltet auf Masse) (vi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
Masse (braun) Lampentest (schaltet auf Masse)(weiss blau) Fernlichtlampe (12V) (weiss) Drehzahl Zündspule (schwarz blau) Blinker rechts (blau scharz) Masse (braun) Blinker links (blau rot) nicht angeschlossen Tachosiganl zum Blinrelais (balu grün) Tachogeber (gelb) Masse Tachobeger (braun) Tachobel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
4.7V
Stromquelle für Gang LEDs. Für mehr als 12mA muss ein Widerstand "R_user" eingelötet werden. Für weniger muss der 1kOhm SMD Widerstand neben R_user entfernt werden I = 12V/1kOhm(default)+12V/R_user I= 12mA (default) + 12V/R_user Beispiel: R_user Strom in LEDs 1 kOhm 22-26mA ohne 11-13mA
Gang 1
Gang 2
Gang 3
Gang 4
Gang 5
Variante "eine LED leuchtet"
Variante "alle LEDs bis und mit Gang X leuchten"
Klemmleisten Ausgang:
Klemmleisten Ausgang:
an Zündungsplus anhängen (Neutral leuchtet wenn Gang 0 eingelegt und Zündschlüssel steckt )
an Ausgang "Neutrallampe" anhängen
Neutrallampe für eigene Ganganzeige
Externe Beschaltung
Anzeige:
nicht bestückt
rising edge trigger A
BAR
RES
BL resistors
Standard panel Fiducial
panel Fiducial with solder mask around fiducial
non retriggerable
retriggerable
